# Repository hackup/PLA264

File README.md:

# PLA264

The PLA264 is a replacement for the MOS 251641-02 PLA chip used in Commodore's TED-based 8-bit computers, the C16, C116, and Plus/4. It is an alternative layout to the [PLA16V8](https://www.freepascal.org/~daniel/c16pla/). Like the original, it is based on the GAL16V8 and it requires the same JED file for programming. Unlike the original, when properly assembled, it is small enough to actually fit into the case of a Commodore Plus/4 without issues.

See my [blog post](https://www.hackup.net/2023/05/how-to-lower-your-pla-the-pla264/) for more details.

There is no warranty whatsoever. **USE AT YOUR OWN RISK!**.

## License
[
](http://creativecommons.org/licenses/by-nc-sa/4.0/)

This work is licensed under a
[Creative Commons Attribution-NonCommercial-ShareAlike 4.0 International License](http://creativecommons.org/licenses/by-nc-sa/4.0/).

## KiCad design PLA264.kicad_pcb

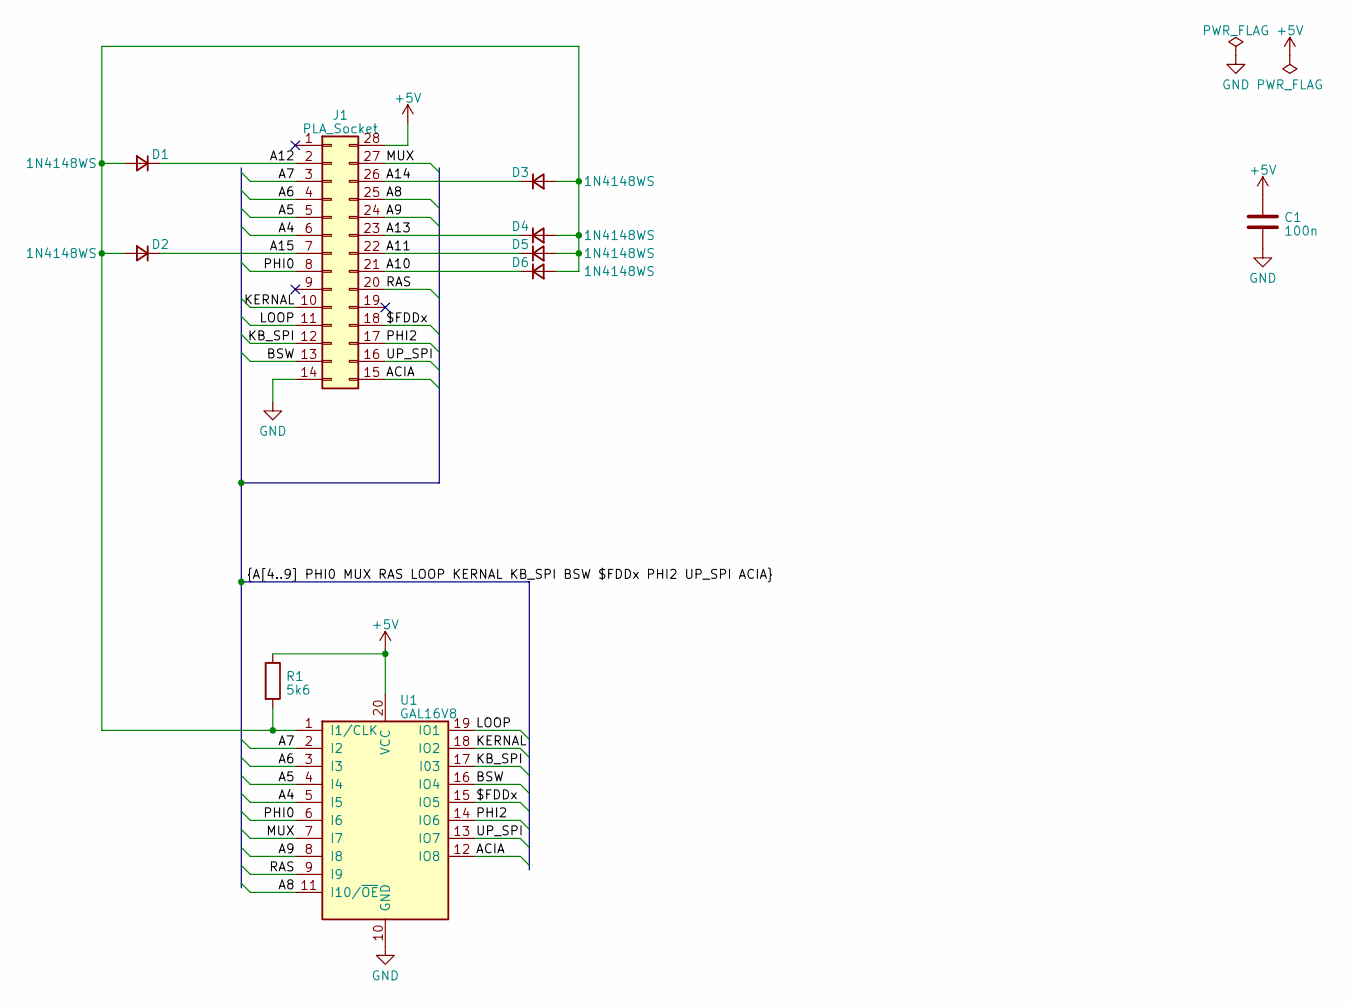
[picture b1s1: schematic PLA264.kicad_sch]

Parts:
C1: 100n; C_0603_1608Metric; LCSC C14663
D1, D2, D3, D4, D5, D6: 1N4148WS; D_SOD-323; LCSC C2128
J1: PLA_Socket; DIP-28_W15.24mm
R1: 5k6; R_0603_1608Metric; LCSC C23189
U1: GAL16V8; DIP-20_W7.62mm

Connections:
+5V: C1.1, J1.28, R1.1, U1.20 (VCC)
/$FDDx: J1.18, U1.15 (IO5)
/A4: J1.6, U1.5 (I5)
/A5: J1.5, U1.4 (I4)
/A6: J1.4, U1.3 (I3)
/A7: J1.3, U1.2 (I2)
/A8: J1.25, U1.11 (I10/~OE)
/A9: J1.24, U1.8 (I8)
/A10: D6.1 (K), J1.21
/A11: D5.1 (K), J1.22
/A12: D1.1 (K), J1.2
/A13: D4.1 (K), J1.23
/A14: D3.1 (K), J1.26
/A15: D2.1 (K), J1.7
/ACIA: J1.15, U1.12 (IO8)
/BSW: J1.13, U1.16 (IO4)
/KB_SPI: J1.12, U1.17 (I03)
/KERNAL: J1.10, U1.18 (IO2)
/LOOP: J1.11, U1.19 (IO1)
/MUX: J1.27, U1.7 (I7)
/PHI0: J1.8, U1.6 (I6)
/PHI2: J1.17, U1.14 (IO6)
/RAS: J1.20, U1.9 (I9)
/UP_SPI: J1.16, U1.13 (IO7)
GND: C1.2, J1.14, U1.10 (GND)
unnamed: D1.2 (A), D2.2 (A), D3.2 (A), D4.2 (A), D5.2 (A), D6.2 (A), R1.2, U1.1 (I1/CLK)

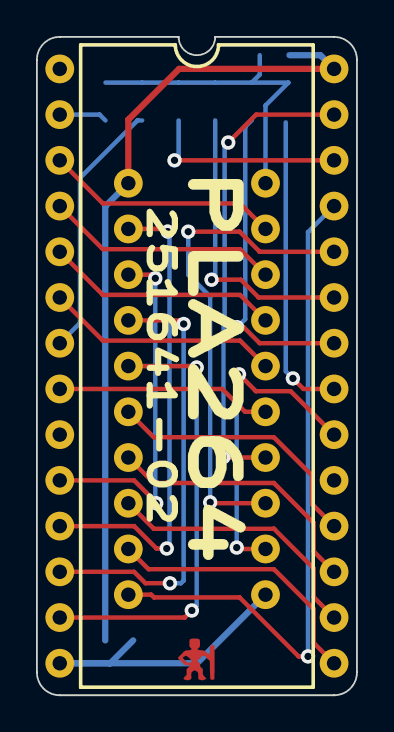
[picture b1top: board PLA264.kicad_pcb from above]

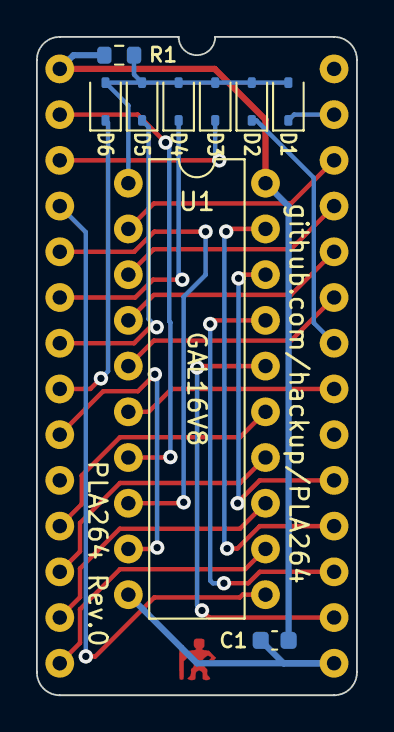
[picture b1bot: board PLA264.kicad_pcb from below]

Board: 2 copper layers, 17.8 x 36.6 mm, 10 parts (9 on the bottom side), 26 nets.

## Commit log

2023-04-25 Initial import.
2023-04-25 Revised layout.
2023-04-25 Cleaning up.
2023-04-25 Preparing for Gerber export.
2023-05-29 Added readme and jedec files.
